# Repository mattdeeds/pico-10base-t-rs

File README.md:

# pico-10base-t-rs

**Software 10BASE-T Ethernet (PIO bit-bang TX *and* RX) and wireless
router on the Raspberry Pi Pico 2 W**. Uses the dual **Hazard3 RISC-V** cores with pure Rust (`no_std`).
A `~$5` micro talks 10 Mbit Ethernet to a real
network with PIO, DMA, a RS-485 transceiver, and magnetics.

Rust port of [C project](https://github.com/mattdeeds/Pico-10BASE-T), which extended
[kingyoPiyo/Pico-10BASE-T](https://github.com/kingyoPiyo/Pico-10BASE-T) (the
original C/PIO Manchester **TX-only** design) with a **RX** path — Manchester
decode over an RS-485 transceiver. This Rust rewrite runs on `rp235x-hal`, exposes
the NIC as a [smoltcp](https://github.com/smoltcp-rs/smoltcp) `phy::Device`, then
grows into a NAPT router with a cyw43 Wi-Fi AP.

## Two builds

The build features give you either layer with no code changes:

- **A standalone software 10BASE-T NIC** (default build): the bit-bang PHY +
  smoltcp. A static-IP host that does ARP / ICMP / UDP / a tiny HTTP server.
- **A wireless router** (`--features router`): the same 10BASE-T as the WAN, a
  cyw43 2.4 GHz AP as the LAN, with L3 forwarding + NAPT between them, a DHCP
  server, and a status page.

## What to expect (performance)

Full detail + method in **[`docs/performance.md`](docs/performance.md)**. Headlines
(measured on real hardware):

| Path | Throughput | Note |
|---|---|---|
| 10BASE-T **TX** (device→host, TCP) | best **~0.95–1.0 MB/s**, typical ~0.4–0.7 | near line rate when clean; half-duplex collision variance |
| 10BASE-T **RX** (host→device, TCP bulk) | **~310 KB/s** @ 0.2% wire loss | stock MTU; ACK-pacing + decode-out-of-IRQ fixes (2026-06) |
| 10BASE-T latency | **~2.6 ms**, 0% loss | |
| Wi-Fi LAN (cyw43 AP) | **~909 down / ~716 up KB/s** | router build |

> **It's a fun software-PHY NIC and a working router, not a
> fast router.** The bit-bang TX is near line rate; RX bulk runs ~310 KB/s
> (the long-suspected "decode/PHY ceiling" turned out to be a fixable
> DMA-starvation bug — see `docs/rx-bulk-ceiling.md` §10). Latency is great;
> ideal for low-rate / IoT-scale traffic.

## Hardware

- **Raspberry Pi Pico 2 W** (RP2350). The plain 10BASE-T NIC build also runs on a
  non-W Pico 2; the Wi-Fi/router builds need the W (cyw43).
- **External 10BASE-T front end:** an **ISL3177E** transceiver + **HR911105A** RJ45
  magnetics. KiCad board design + gerbers/BOM are in [`hardware/`](hardware/).

| Signal | Pico 2 pin |
|---|---|
| ISL3177E `RO` (receiver out → MCU) | GP13 |
| ISL3177E `DI` (driver in ← MCU) | GP14 |
| Onboard LED (heartbeat, NIC build) | GP25 |
| SWD debug probe | SWCLK / SWDIO / GND |

## Toolchain

- Rust ≥ 1.82, target `riscv32imac-unknown-none-elf`
  (`rustup target add riscv32imac-unknown-none-elf`).
- Flashing: [picotool](https://github.com/raspberrypi/picotool) (USB), or OpenOCD
  over SWD:
  `openocd -f interface/cmsis-dap.cfg -f target/rp2350-riscv.cfg -c "program <elf> verify reset exit"`.

## Build & flash

```bash
# Standalone 10BASE-T NIC (static IP 192.168.37.24) — the default build
cargo build --release
cargo run   --release            # flashes via the .cargo/config.toml runner

# Other variants
cargo build --release --features wan-dhcp    # NIC as a DHCP client (WAN-style)
cargo build --release --features wireless    # cyw43 AP only (no wired side)
cargo build --release --features router      # WAN(10BT) + LAN(Wi-Fi) + NAPT router
```

The device logs status over **USB CDC** (assert DTR to read it): `[R2b]` heartbeat,
`[Rx]` decode stats, and on the router build `[Cyw43]` / `[Wan]` / `[Fwd]` / `[Nat]`
/ `[Perf]` lines.

### Wired host setup (10BASE-T peer)

The device emits Normal Link Pulses only (no auto-negotiation), so force the peer
NIC to 10 Mbit half-duplex:

```bash
sudo ethtool -s <iface> speed 10 duplex half autoneg off
sudo ip addr add 192.168.37.19/24 dev <iface>
```

### Router credentials

The cyw43 AP SSID/passphrase are **compile-time placeholders** in
`src/wireless.rs` (`AP_SSID` / `AP_PASSPHRASE = "change-me-please"`). **They should be changed.**

## How it works

- **PIO0** drives the 10BASE-T PHY: **SM0** = 20 MHz Manchester TX (256-entry
  lookup table → single-ended on GP14), **SM1** = 60 MHz RX sampler (`in pins, 1`,
  3 samples/half-bit), **SM2** = a carrier-detect SM for the half-duplex CSMA/CA
  TX gate.
- **DMA** ferries the RX sampler into a double-buffer; **core 1** owns the
  `DMA_IRQ_0` handler running an **edge-tracking DPLL Manchester decoder** + FCS
  (re-anchors to each mid-bit transition to cancel clock drift).
- **core 0** runs smoltcp (the control plane) and, on the router build, an
  **embassy executor** hosting the cyw43 `Runner`, the LAN/WAN net tasks, and the
  custom L3 forwarding + NAPT data path. **PIO1** is a custom gSPI transport to the
  cyw43 radio.
- An **RP2350 hardware watchdog** auto-reboots + recovers the device if the loop
  ever wedges (a known intermittent hang under sustained full-MTU inbound).

## Repo layout

The package is **a library + a binary**: the transport core is a reusable
library crate that other projects can take as a Cargo dependency (e.g.
[pico-remote-probe](https://github.com/mattdeeds/pico-remote-probe), a
network-attached SWD debug probe, uses it as its NIC); the router application
in `src/main.rs` is the in-tree consumer.

- `src/lib.rs` — the **library**: `eth_tx`, `eth_rx`, `eth_rx_dpll`, `eth_mac`,
  `manchester`, `crc` (the **10BASE-T bit-bang NIC**, PHY + MAC), plus
  `multicore_riscv` (Hazard3 core-1 launch), `pico_reset` (picotool USB reset),
  `pio_util`, and — behind the `cyw43-phy` feature — `cyw43_phy` (a smoltcp
  `phy::Device` over the cyw43 radio, no executor required).
- `src/main.rs`, `src/wireless.rs`, `src/forward.rs`, `src/conntrack.rs`,
  `src/dhcp_server.rs`, `src/wan.rs` — the **router** (cyw43 + forwarding + NAPT).
- `docs/` — a thorough **engineering log** (how this was built + characterized).
  Start with [`docs/README.md`](docs/README.md).
- `tools/` — host-side measurement scripts.

## Limitations

Half-duplex (by MAC policy; the transceiver is FD-*capable* but FD only helps
contended traffic); no auto-negotiation; RX bulk ~310 KB/s (next bounds:
decode CPU time and the DMA half-fill ACK-latency floor — see
`docs/rx-bulk-ceiling.md` §10). A hardware watchdog guards against hangs
(the old full-MTU-inbound wedge stopped reproducing after the 2026-06 RX
restructure, but the watchdog stays).
Just an educational project, please don't replace your home router with this.

## Credits

- [kingyoPiyo/Pico-10BASE-T](https://github.com/kingyoPiyo/Pico-10BASE-T) — the
  original C/PIO 10BASE-T **TX** design (MIT, Copyright © 2022 kingyo). This project
  is a Rust port of the author's own
  [C project](https://github.com/mattdeeds/Pico-10BASE-T), which extended
  kingyoPiyo's work with the **RX** path (Manchester decode over an RS-485
  transceiver).
- [Niccle](https://github.com/timonvo/niccle) — a reference for the
  Manchester RX decode approach and circuit design.
- [embassy](https://github.com/embassy-rs/embassy) `cyw43` driver + firmware blobs
  (Infineon permissive binary license — see `cyw43-firmware/`).
- [smoltcp](https://github.com/smoltcp-rs/smoltcp), [rp235x-hal](https://github.com/rp-rs/rp-hal).

## License

Dual-licensed under either **MIT** ([LICENSE-MIT](LICENSE-MIT)) or
**Apache-2.0** ([LICENSE-APACHE](LICENSE-APACHE)), at your option. The cyw43
firmware blobs in `cyw43-firmware/` carry their own (Infineon) permissive license.

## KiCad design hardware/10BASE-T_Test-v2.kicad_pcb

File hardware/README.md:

# Hardware — 10BASE-T front-end board

KiCad project for the **10BASE-T analog front end** used by this project (and by
its [C ancestor](https://github.com/mattdeeds/Pico-10BASE-T)). It breaks an
**ISL3177E** RS-485 transceiver and an **HR911105A** RJ45 jack (integrated
magnetics) out to single-ended GP13 (RX) / GP14 (TX) on a Raspberry Pi Pico 2, so
the Pico's PIO can both drive and receive a real 10BASE-T differential line.

The circuit is based on the [Niccle](https://github.com/timonvo/niccle) reference
design. This is `v2` — a small prototype/test board, not a product.

> ⚠️ **Do not connect this to PoE equipment.** It's an educational software-PHY
> front end with no isolation guarantees beyond the magnetics.

## How it works

The ISL3177E is an RS-485 transceiver repurposed as a 10BASE-T line driver +
slicer:

- **TX:** Pico `GP14` → `DI` (driver input) → differential `Y`/`Z` → AC-coupling →
  HR911105A magnetics → RJ45 TX pair.
- **RX:** RJ45 RX pair → magnetics → differential `A`/`B` → `RO` (receiver output,
  single-ended Manchester) → Pico `GP13`, where the PIO sampler + software DPLL
  decode it.

See the repo's top-level [`README.md`](../README.md) ("How it works") for the
firmware side and the exact Pico pin map.

## Bill of materials

| Ref | Value | Footprint | Role |
|---|---|---|---|
| U1 | **ISL3177EIBZ** | SOIC-8 | RS-485 transceiver (TX driver + RX slicer) |
| J6 | **HR911105A** | RJ45 (Hanrun, horizontal) | jack + integrated magnetics |
| C5, C8, C9 | 100 nF | 0603 | supply decoupling |
| C6, C7 | 10 nF | 0603 | AC-coupling to the line |
| R28 | 100 Ω | 0603 | differential line termination |
| R29, R30 | 50 Ω | 0603 | source termination |
| J1 | 1×02 header | 2.54 mm | power (3V3 / GND) |
| J2, J3 | 1×04 header | 2.54 mm | signal / Pico connections |

(Source of truth: [`production/bom.csv`](production/bom.csv).)

## Files

- `10BASE-T_Test-v2.kicad_pro` / `.kicad_sch` / `.kicad_pcb` — the KiCad 10 project
  (schematic + PCB). Open `.kicad_pro` in KiCad.
- `production/` — fabrication outputs:
  - `10BASE-T_Test-v2.zip` — Gerbers + drill files (2-layer board), ready to send
    to any board house.
  - `bom.csv` — bill of materials.
  - `positions.csv` — pick-and-place / centroid (for assembly).
  - `designators.csv`, `netlist.ipc` — supporting fab data.

## Fabricating it

Upload `production/10BASE-T_Test-v2.zip` to a PCB fab (JLCPCB, PCBWay, OSH Park,
etc.) as a standard 2-layer board. For assembly, supply `bom.csv` + `positions.csv`.
To regenerate any of these, re-run the export from KiCad (the
[Fabrication Toolkit](https://github.com/bennymeg/Fabrication-Toolkit) settings
used are in `fabrication-toolkit-options.json`).

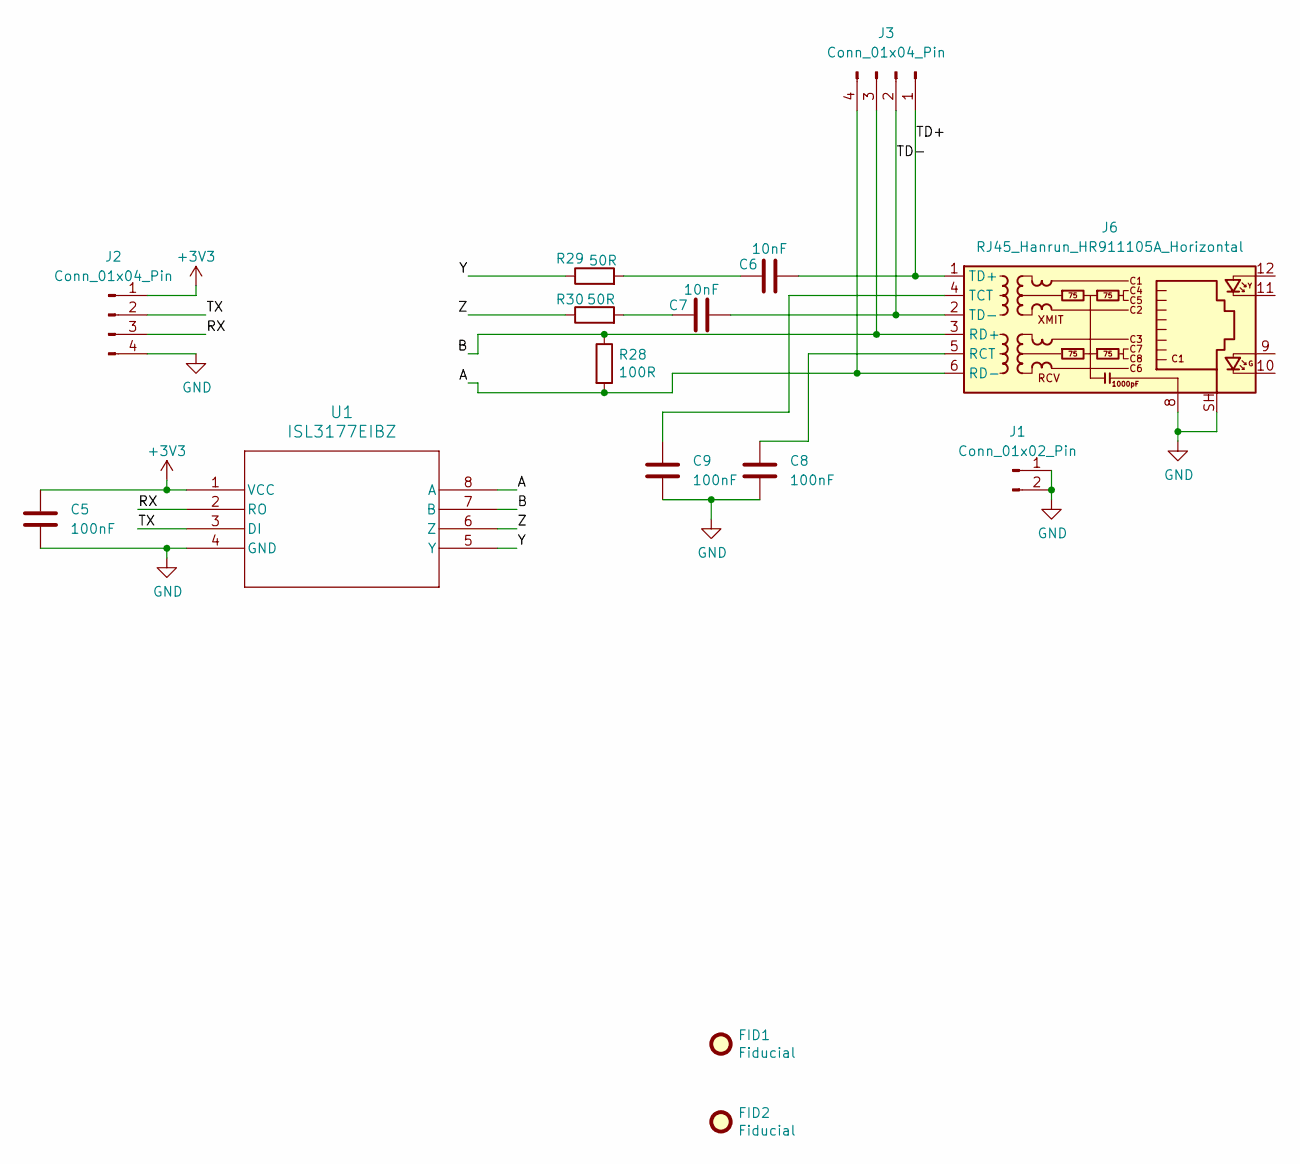
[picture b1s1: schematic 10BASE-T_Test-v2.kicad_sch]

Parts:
C5, C8, C9: 100nF; C_0603_1608Metric
C6, C7: 10nF; C_0603_1608Metric
FID1, FID2: Fiducial; Fiducial_1mm_Mask2mm
J1: Conn_01x02_Pin; PinHeader_1x02_P2.54mm_Vertical
J2, J3: Conn_01x04_Pin; PinHeader_1x04_P2.54mm_Vertical
J6: RJ45_Hanrun_HR911105A_Horizontal
R28: 100R; R_0603_1608Metric
R29, R30: 50R; R_0603_1608Metric
U1: ISL3177EIBZ; SOIC_177EIBZ_REN

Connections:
+3V3: C5.1, J2.1, U1.1 (VCC)
/A: J3.4, J6.6 (RD-), R28.2, U1.8 (A)
/B: J3.3, J6.3 (RD+), R28.1, U1.7 (B)
/RX: J2.3, U1.2 (RO)
/TD+: C6.2, J3.1, J6.1 (TD+)
/TD-: C7.2, J3.2, J6.2 (TD-)
/TX: J2.2, U1.3 (DI)
/Y: R29.1, U1.5 (Y)
/Z: R30.1, U1.6 (Z)
GND: C5.2, C8.2, C9.2, J1.1, J1.2, J2.4, J6.8, J6.SH, U1.4 (GND)
unnamed: C6.1, R29.2
unnamed: C7.1, R30.2
unnamed: C8.1, J6.5 (RCT)
unnamed: C9.1, J6.4 (TCT)

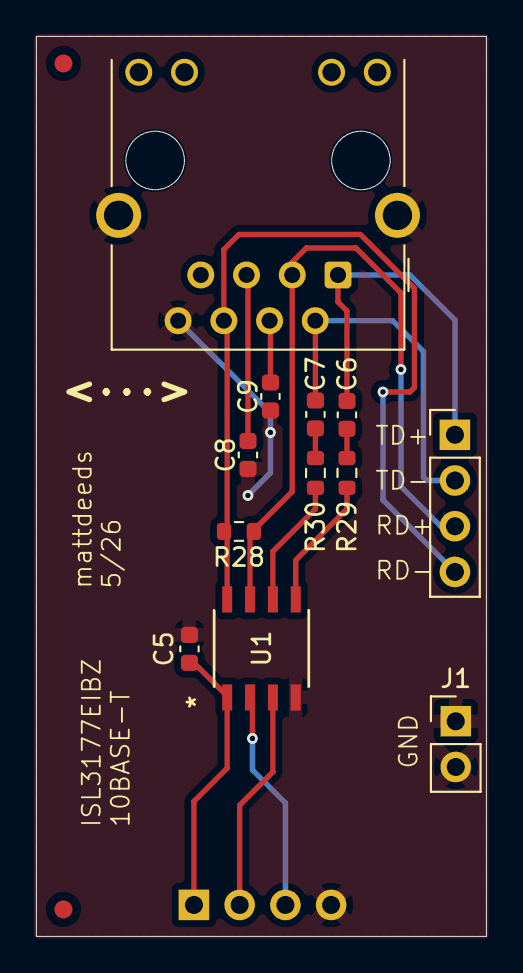
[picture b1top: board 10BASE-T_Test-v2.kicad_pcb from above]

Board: 2 copper layers, 25.0 x 50.0 mm, 15 parts (1 on the bottom side), 14 nets.

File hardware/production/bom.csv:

Designator,Footprint,Quantity,Value,LCSC Part #
"C5, C8, C9",0603,3,100nF,
"C6, C7",0603,2,10nF,
J1,PinHeader_1x02_P2.54mm_Vertical,1,Conn_01x02_Pin,
"J2, J3",PinHeader_1x04_P2.54mm_Vertical,2,Conn_01x04_Pin,
J6,RJ45_Hanrun_HR911105A_Horizontal,1,RJ45_Hanrun_HR911105A_Horizontal,
R28,0603,1,100R,
"R29, R30",0603,2,50R,
U1,SOIC_177EIBZ_REN,1,ISL3177EIBZ,

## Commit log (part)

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2026-05-28 docs(router-plan §11): R13 on-board findings + pivot plan to proven cyw43 driver
    Capture the on-board result (10BT verified on Pico 2 W; gSPI bit-bang probe
    reads varying/floating data → chip not responding; pins + funcsel ruled out;
    SPI lines unscoppable as they're off-header) and the decided pivot to the proven
    cyw43 driver + a faithful self-contained FIFO-driven PIO gSPI transport. Notes
    that the proven driver's init doubles as the (currently-unverified) board's
    hardware test, and lays out the next-session build (PIO transport, async
2026-05-28 RESUME: refresh "next session" callout for R13 status (verify board → pivot)
    The callout still said "router scoped, R13 next" — stale after the on-board
    work. Update it to the real starting point: on branch r13-wireless-scaffold,
    10BT verified on the Pico 2 W, cyw43/async foundation compiles+links, but the
    gSPI bit-bang probe shows the chip not responding (pins+funcsel ruled out, board
    wireless UNVERIFIED). FIRST ACTION = verify the board with stock MicroPython
    (LED + WLAN scan); THEN pivot to the proven cyw43 driver + PIO transport.
2026-06-02 R18/R19a cleanup (post-review): dedup ARP prefix, POOL_LEN-sized body, mac_str
    Behavior-preserving cleanups from the code review (no correctness changes):
    - forward.rs: the 6-byte Ethernet/IPv4 ARP header prefix was written by
    build_arp_request and matched by learn() as two separate literals. Extract a
    single `const ARP_ETH_IPV4_PREFIX` so the writer and parser can't drift.
    - dhcp_server.rs / wireless.rs: the mgmt-page body String capacity was a magic
    1792 justified by a hand comment. Make POOL_LEN `pub` and derive the cap from
2026-06-02 docs: note the post-review cleanup in RESUME
    Record the high-effort code review of R18+R19a (no correctness bugs) and the
    three behavior-preserving idiom fixes applied (29a7003): ARP-prefix const,
    POOL_LEN-derived status body, shared mac_str. Board callout updated.
2026-06-02 docs: scope low-power (roadmap E) — characterize-first plan, meter-gated
    docs/low-power-plan.md: the turnkey characterization plan to run once a power
    meter is wired — a measurement matrix that A/Bs each lever (240 vs 150 MHz, VREG
    steps, radio-off/sampler-off diagnostic builds, carrier-gated sampler, cyw43 PM;
    idle vs load), grounded in the current config (always-on 60 MHz sampler + DMA
    waking core 1; cyw43 AP PM::None; 240 MHz overclock at default VREG). Explicit
    "characterize first — no functional power changes until a measurement justifies
2026-06-02 instr: routed-throughput + drop diagnostics (perf characterization, step 1)
    First instrumentation increment toward characterizing the full routed/NAT'd path
    (WiFi client -> NAPT -> 10BT WAN) — which the R11/R12 numbers never covered (those
    were the 10BT NIC in isolation).
    forward.rs data-plane counters:
    - per-direction egressed bytes (FWD_BYTES_TO_WAN/LAN) for throughput
    - FWD_DROP split by cause (qfull / no-nexthop / nat-exhaust / tx-busy / other)
2026-06-02 docs: pivot to performance characterization; backburner low-power; pin backlog
    Low-power is scoped but backburnered (gated on a power meter). New active track:
    characterize the routed/NAT'd path (WiFi client -> NAPT -> 10BT WAN), which has
    never been measured (R11/R12 were the 10BT NIC in isolation) -> find the throughput
    ceiling, which decides whether the throughput-motivated radio modularization is
    worth it.
    - docs/perf-characterization-plan.md: the plan-of-record (goal, instrumentation
2026-06-10 Fix RX-of-bulk ceiling: stop advertising a 1-segment TCP window
    smoltcp clamps every advertised TCP receive window to max_burst_size x MSS
    (iface/packet.rs). EthMac::capabilities() set max_burst_size = Some(1), so
    the device advertised a one-segment window on every ACK regardless of the
    32 KB sink buffer. With a 1-MSS window, smoltcp's immediate-ACK rule can
    never fire (it needs >1 MSS of unACKed data), so every bulk segment paid
    the full 10 ms delayed-ACK timer + RTT.
